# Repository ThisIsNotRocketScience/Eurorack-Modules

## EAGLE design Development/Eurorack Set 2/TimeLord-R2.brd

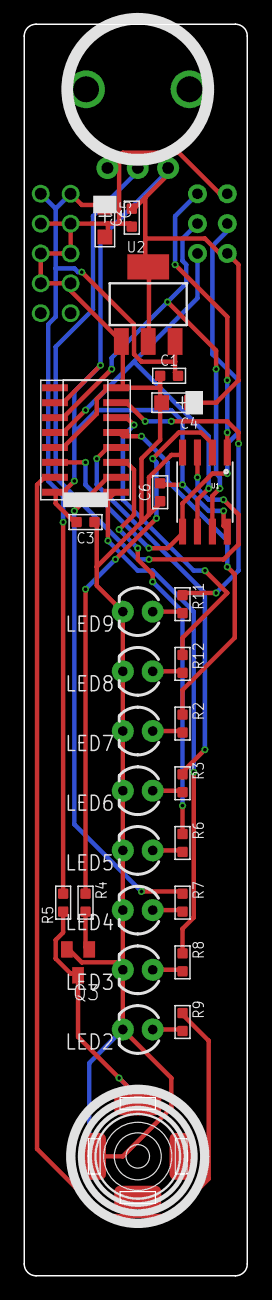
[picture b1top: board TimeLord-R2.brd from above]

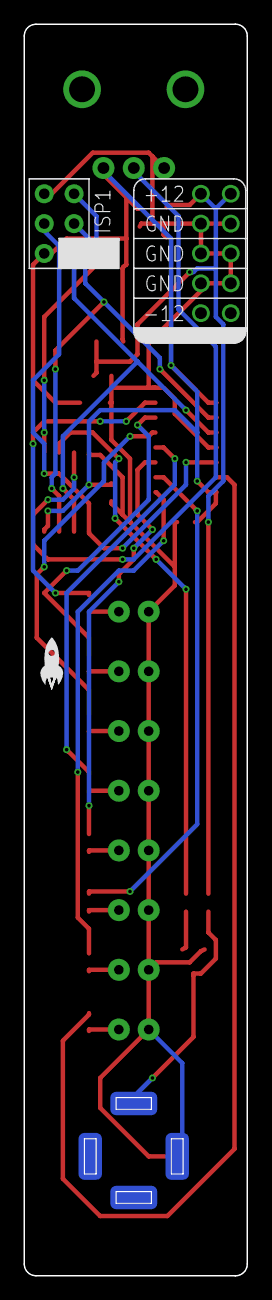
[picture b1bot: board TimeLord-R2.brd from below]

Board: 2 copper layers, 19.0 x 106.5 mm, 34 parts (3 on the bottom side), 27 nets.

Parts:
C1, C2, C3, C6: 100nF; C0603
C4, C5: 10uF; AVX-A
IC2: IC_74HC595-SOIC-16; SOIC-16
ISP1: AVRISP-6; AVRISP
LED2, LED3, LED4, LED5, LED6, LED7, LED8, LED9: WHITE; LED3MM
Q3: MMBT3904; SOT23-BEC
R2, R3, R6, R7, R8, R9, R11, R12: 50; R0603
R4: 100k; R0603
R5: 10k; R0603
U1: Tiny85-20-SMT; SO08-EIAJ
U2: CJ1117-5.0-1310170P1; SOT223
U$1: POWER_SIMPLE10-OTHERSIDE; POWER_10_LABELSOTHERSIDE
U$2: EURORACK_PCB4HP; EURORACK4HPPCB
U$3: CLOCK; 3.5MM-JACK-SWITCH-13MM-OUTPUT
U$4: SPEED; OG-POTS_ALPS_POT_VERTICAL
U$5: JUSTATINYROCKET

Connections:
5V: C2.2, C3.2, C4.+, C6.2, IC2.10, IC2.16, ISP1.2, U1.8, U2.2, U2.TER, U$4.P$3
12V: C1.2, C5.+, R5.2, U2.3, U$1.9, U$1.10
CLOCKJACK: Q3.C, R5.1, U$3.TIP@1, U$3.TIP@2
CLOCKOUT: R4.1, U1.2
CLOCKPOT: U1.3, U$4.P$2
GND: C1.1, C2.1, C3.1, C4.-, C5.-, C6.1, IC2.8, IC2.13, ISP1.6, LED2.K, LED3.K, LED4.K, LED5.K, LED6.K, LED7.K, LED8.K, LED9.K, Q3.E, U1.4, U2.1, U$1.3, U$1.4, U$1.5, U$1.6, U$1.7, U$1.8, U$3.RING@1, U$3.RING@2, U$4.P$1
LEDB1: IC2.15, R9.1
LEDB2: IC2.1, R8.1
LEDB3: IC2.2, R7.1
LEDB4: IC2.3, R6.1
LEDB5: IC2.4, R3.1
LEDB6: IC2.5, R2.1
LEDB7: IC2.6, R12.1
LEDB8: IC2.7, R11.1
LEDCLOCK: IC2.11, ISP1.3, U1.7
LEDDAT: IC2.14, ISP1.4, U1.5
LEDLATCH: IC2.12, ISP1.1, U1.6
unnamed: LED9.A, R11.2
unnamed: LED8.A, R12.2
unnamed: LED7.A, R2.2
unnamed: LED6.A, R3.2
unnamed: LED5.A, R6.2
unnamed: LED4.A, R7.2
unnamed: LED3.A, R8.2
unnamed: LED2.A, R9.2
unnamed: Q3.B, R4.2
RESET: ISP1.5, U1.1

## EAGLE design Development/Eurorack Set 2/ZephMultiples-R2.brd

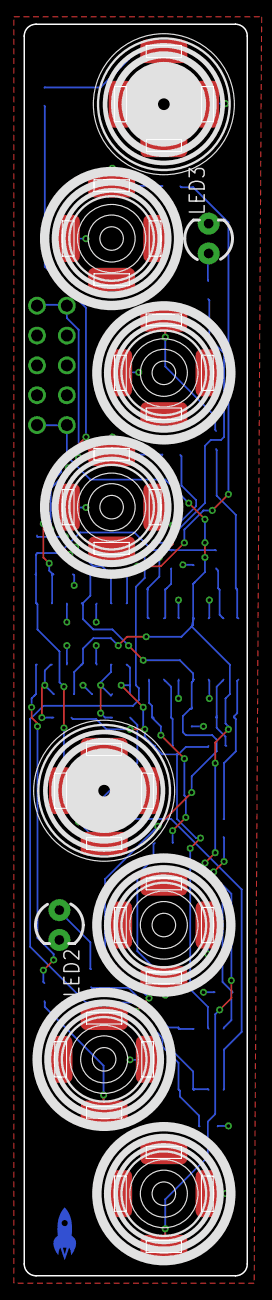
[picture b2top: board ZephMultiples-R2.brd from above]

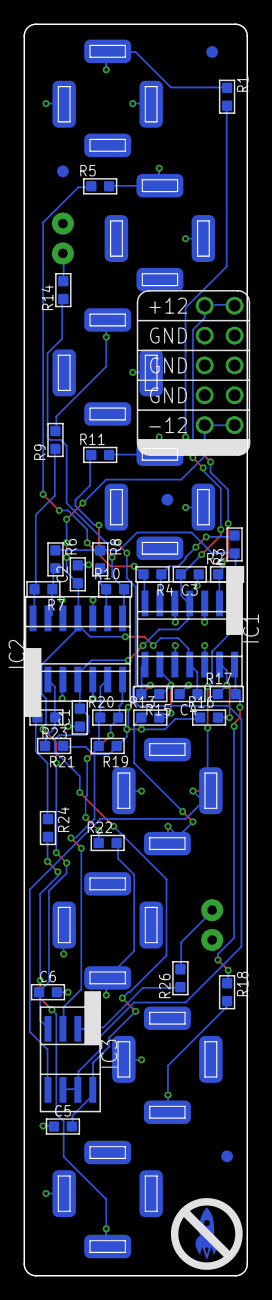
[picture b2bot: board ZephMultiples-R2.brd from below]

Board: 2 copper layers, 19.0 x 106.5 mm, 50 parts (39 on the bottom side), 31 nets.

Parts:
C1, C2, C3, C4, C5, C6: 100n; C0603
I1: In 1; 3.5MM-JACK-SWITCH-13MM-INPUT
I2: In 2; 3.5MM-JACK-SWITCH-13MM-INPUT
IC1, IC2: TL074D; SO14
IC3: TL072; SO08
LED2, LED3: REDBLUE; LED3MM
O1-1, O1-2, O1-3, O2-1, O2-2, O2-3: 3.5MM-JACK-SWITCH-13MM-OUTPUT
R1, R2, R3, R4, R6, R7, R8, R10, R13, R15, R16, R17, R19, R20, R21, R23: 100k; R0603
R5, R9, R11, R18, R22, R24: 51; R0603
R14, R26: 1k; R0603
U$1: SMALLROCKET
U$2, U$3, U$4, U$5: FIDUCIAL; FIDUCIAL_1MM
U$15: EURORACK_PCB4HP; EURORACK4HPPCB
U$16: POWER_SIMPLE10-OTHERSIDE; POWER_10_LABELSOTHERSIDE

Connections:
12V: C1.2, C3.2, C5.2, IC1.4, IC2.4, IC3.8, U$16.9, U$16.10
-12V: C2.1, C4.1, C6.1, IC1.11, IC2.11, IC3.4, U$16.1, U$16.2
GND: C1.1, C2.2, C3.1, C4.2, C5.1, C6.2, I1.RING@1, I1.RING@2, I1.SWITCH@1, I1.SWITCH@2, I2.RING@1, I2.RING@2, IC1.3, IC1.5, IC1.10, IC1.12, IC2.3, IC2.5, IC2.10, IC2.12, LED2.K, LED3.K, O1-1.RING@1, O1-1.RING@2, O1-2.RING@1, O1-2.RING@2, O1-3.RING@1, O1-3.RING@2, O2-1.RING@1, O2-1.RING@2, O2-2.RING@1, O2-2.RING@2, O2-3.RING@1, O2-3.RING@2, U$16.3, U$16.4, U$16.5, U$16.6, U$16.7, U$16.8
LED2DRIVE: IC3.6, IC3.7, R14.1
LED3DRIVE: IC3.1, IC3.2, R26.1
unnamed: I1.TIP@1, I1.TIP@2, R1.1
unnamed: IC1.2, R1.2, R2.1
unnamed: I2.SWITCH@1, I2.SWITCH@2, IC1.1, IC3.5, R2.2, R3.1, R6.1, R8.1
unnamed: IC1.6, R3.2, R4.1
unnamed: IC1.7, R4.2, R5.1
unnamed: IC2.13, R6.2, R7.1
unnamed: IC2.9, R8.2, R10.1
unnamed: IC2.14, R7.2, R9.1
unnamed: IC2.8, R10.2, R11.1
unnamed: LED3.A, R14.2
unnamed: O1-1.TIP@1, O1-1.TIP@2, R5.2
unnamed: O1-2.TIP@1, O1-2.TIP@2, R9.2
unnamed: O1-3.TIP@1, O1-3.TIP@2, R11.2
unnamed: I2.TIP@1, I2.TIP@2, R13.1
unnamed: IC1.9, R13.2, R15.1
unnamed: IC1.8, IC3.3, R15.2, R16.1, R19.1, R21.1
unnamed: IC1.13, R16.2, R17.1
unnamed: IC1.14, R17.2, R18.1
unnamed: IC2.6, R19.2, R20.1
unnamed: IC2.2, R21.2, R23.1
unnamed: IC2.7, R20.2, R22.1
unnamed: IC2.1, R23.2, R24.1
unnamed: LED2.A, R26.2
unnamed: O2-1.TIP@1, O2-1.TIP@2, R18.2
unnamed: O2-2.TIP@1, O2-2.TIP@2, R22.2
unnamed: O2-3.TIP@1, O2-3.TIP@2, R24.2

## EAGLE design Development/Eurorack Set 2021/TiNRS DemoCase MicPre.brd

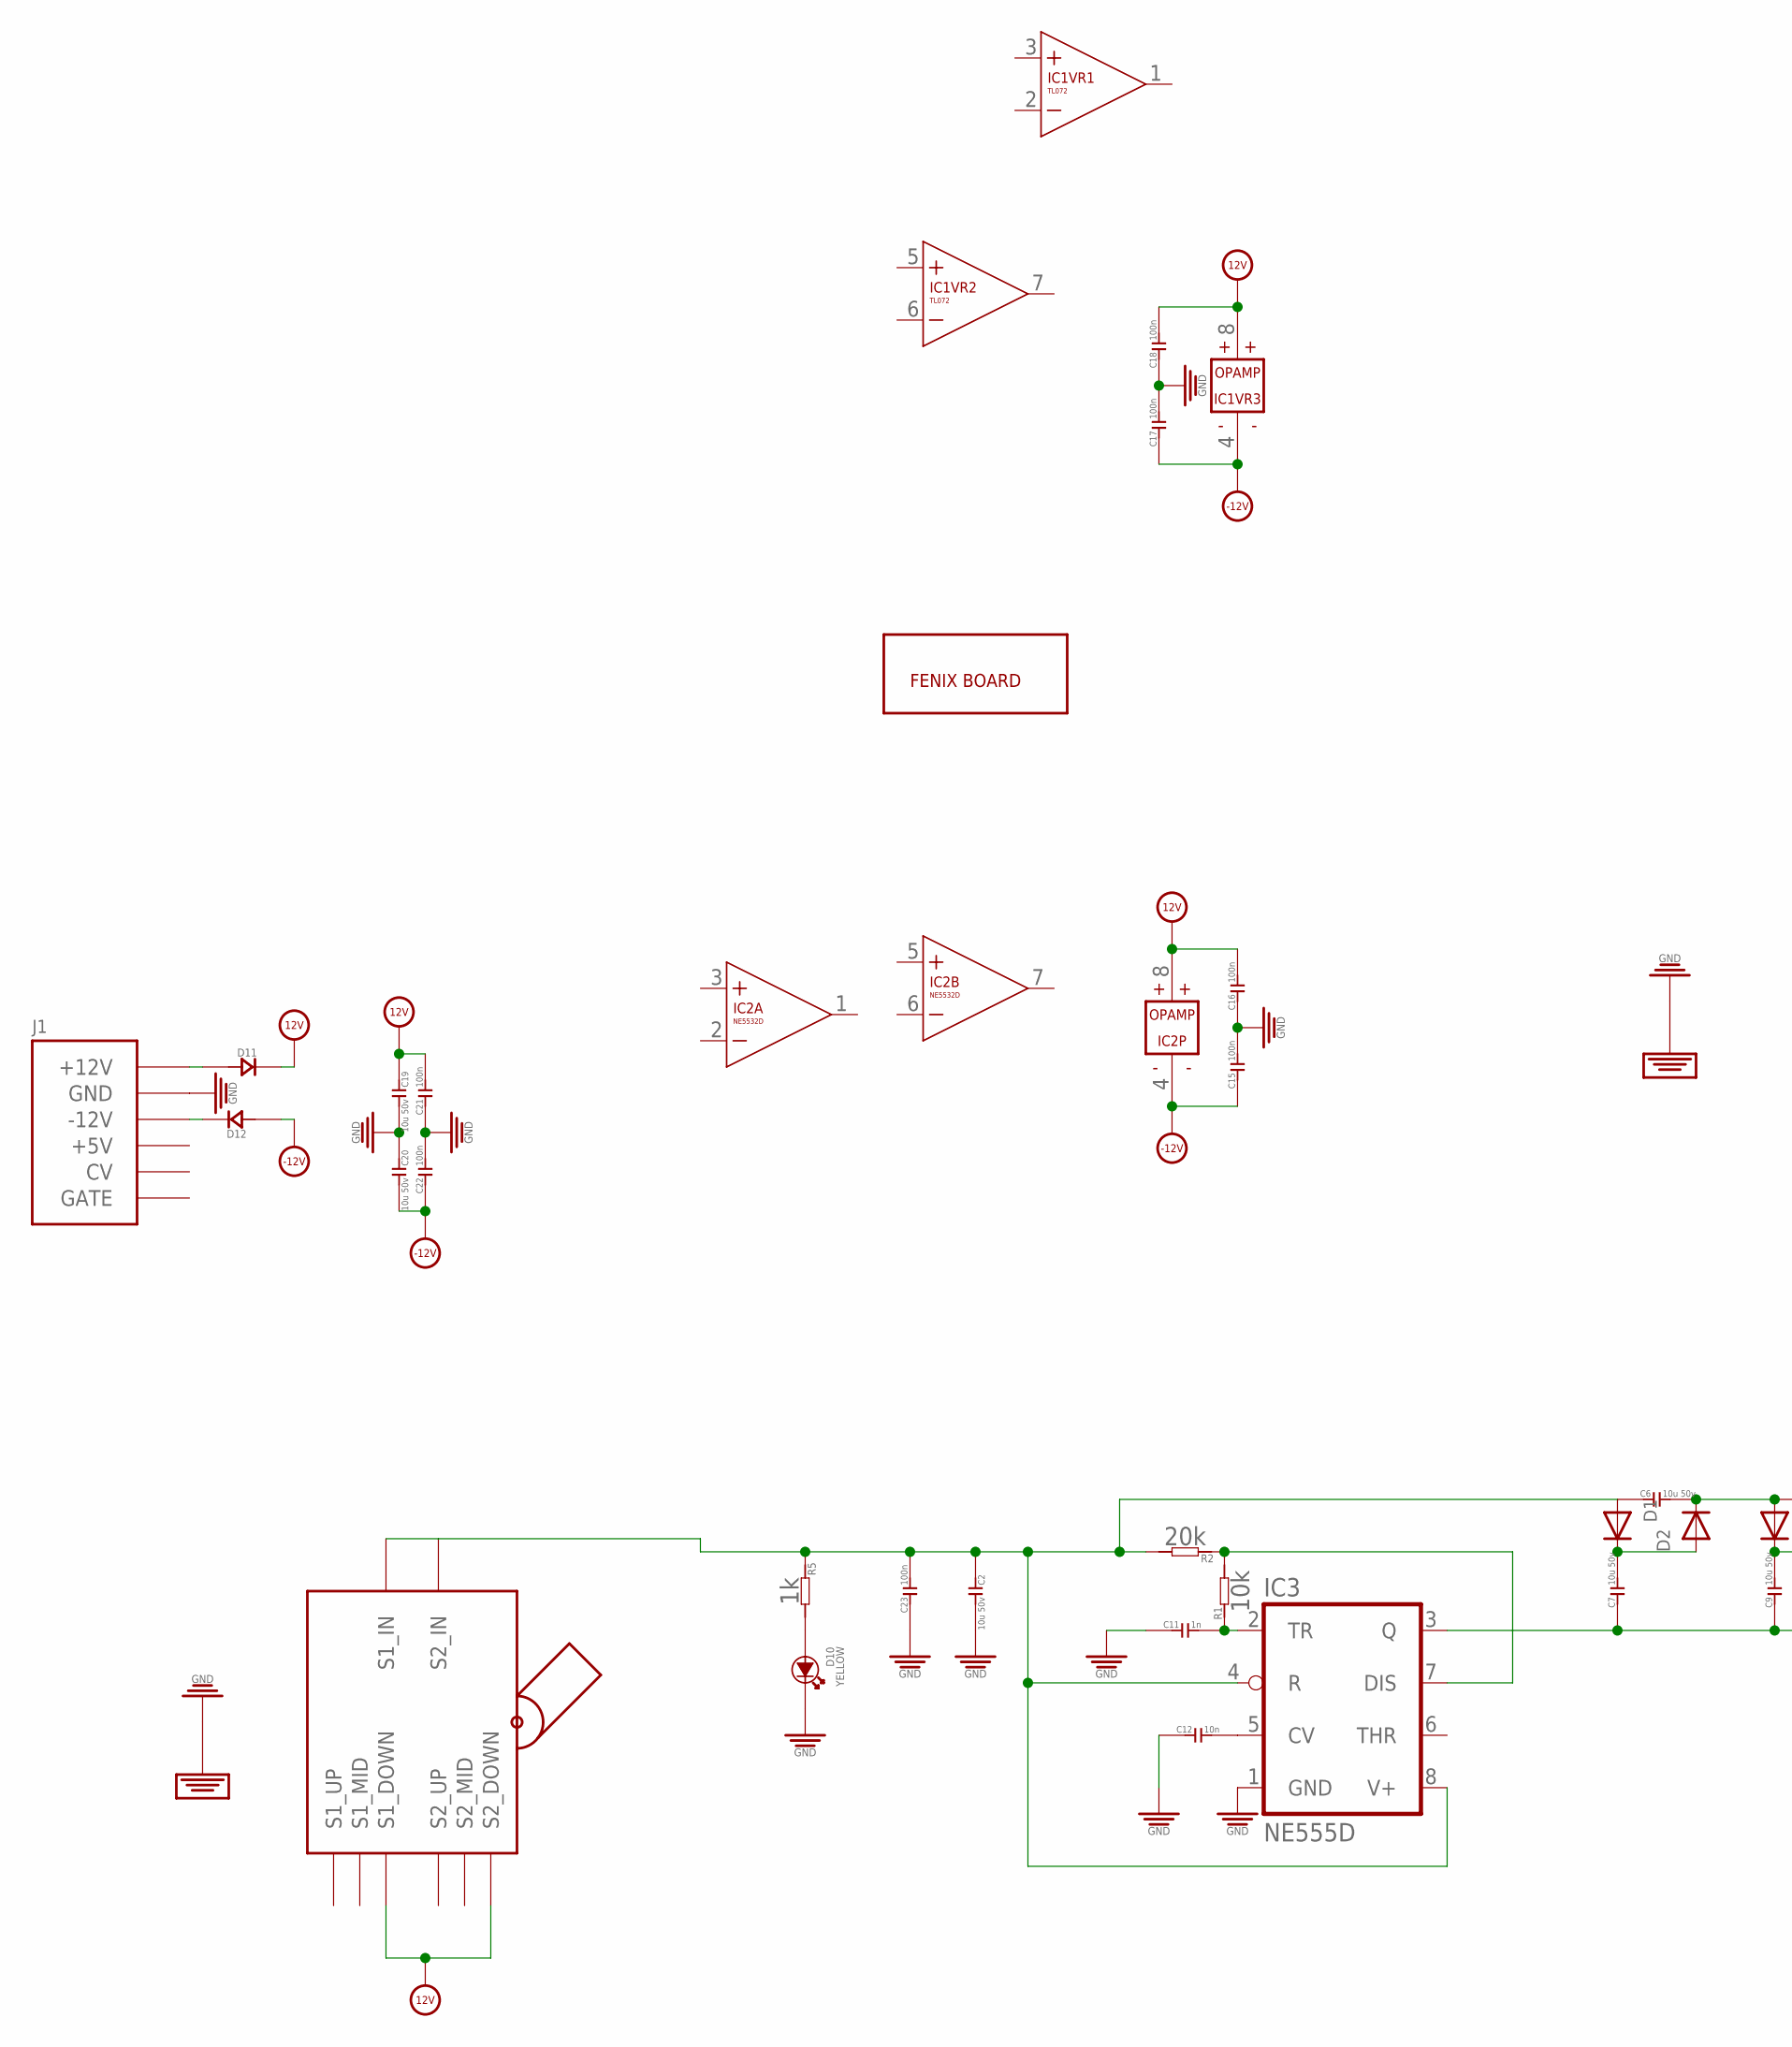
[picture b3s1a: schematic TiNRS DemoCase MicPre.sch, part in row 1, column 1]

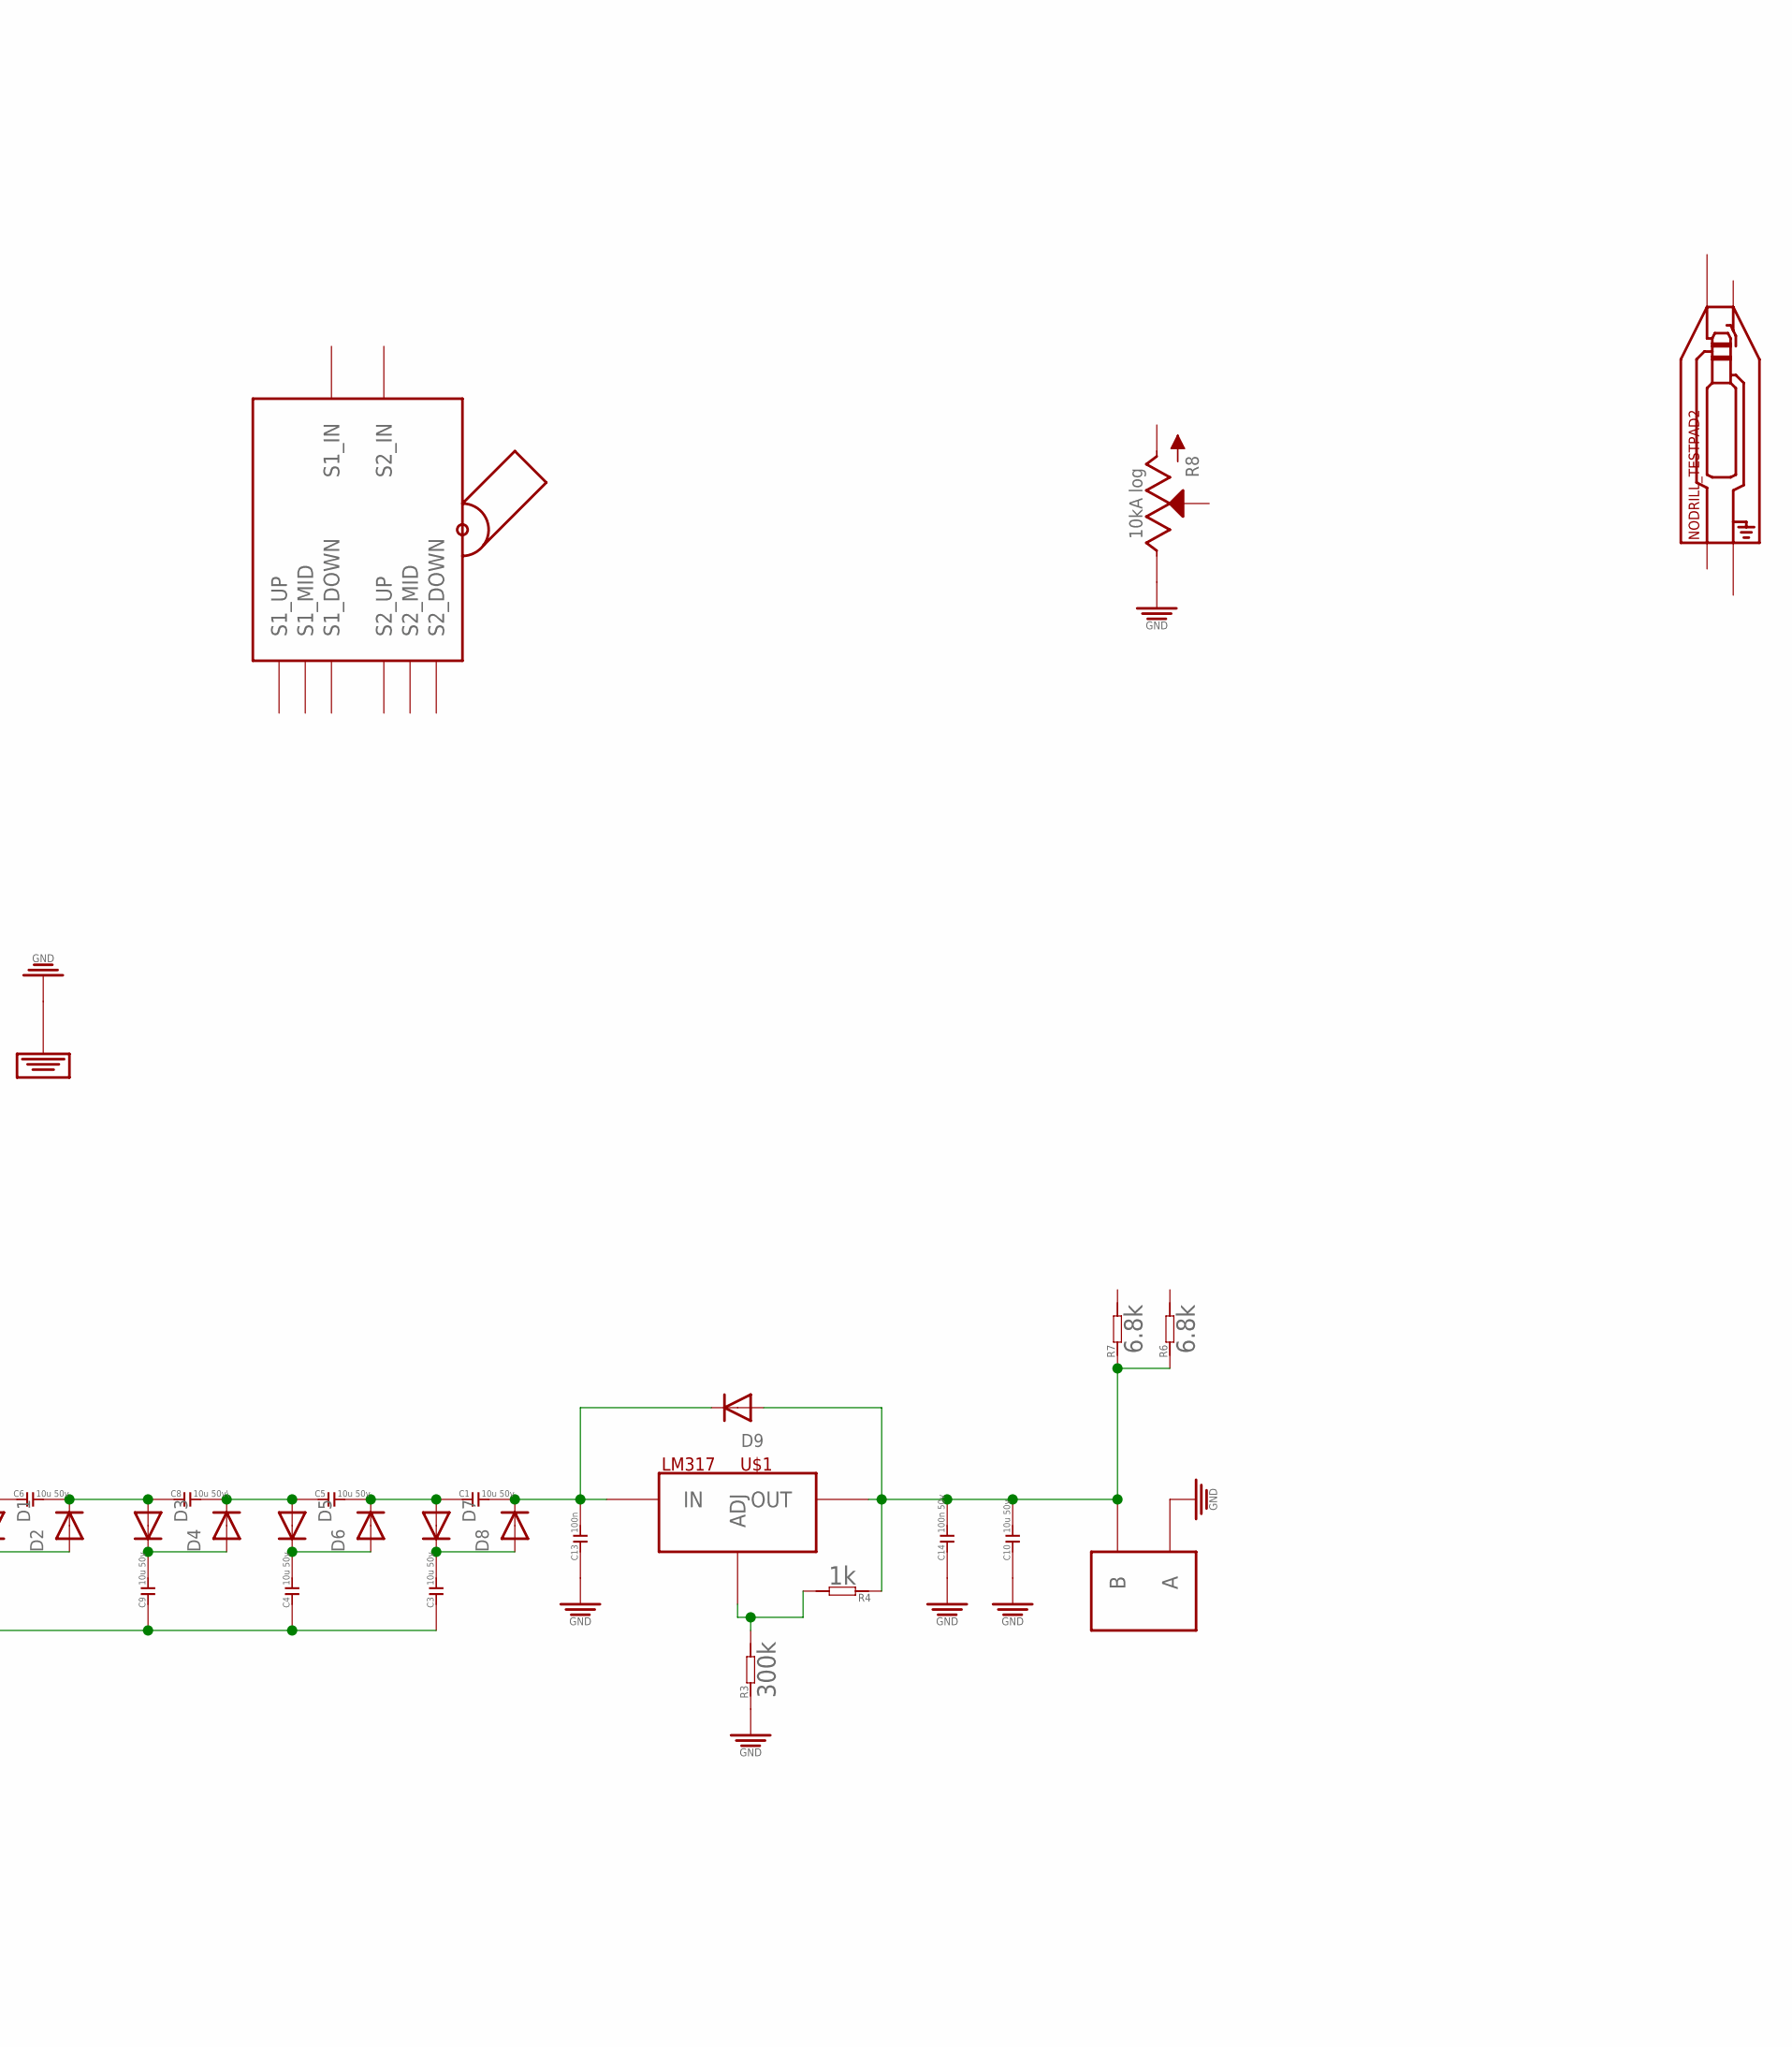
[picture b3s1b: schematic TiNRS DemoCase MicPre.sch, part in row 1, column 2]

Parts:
C1, C2, C3, C4, C5, C6, C7, C9, C10, C19, C20: 10u 50v; C3216
C8: 10u 50v\; C3216
C11: 1n; C0603
C12: 10n; C0603
C13, C15, C16, C17, C18, C21, C22, C23: 100n; C0603
C14: 100n 50v; C0603
D1, D2, D3, D4, D5, D6, D7, D8, D9: DIODESOD-123; SOD-123
D10: YELLOW; 3MMLED
D11, D12: D-SMA; DO-214AC
IC1: TL072; SO08
IC2: NE5532D; SO08
IC3: NE555D; SO08
J1: POWER_SHROUDED_NOTEXT; POWER_16_SHROUDED_NOTEXT
NODRILL_TESTPAD2: AUDIO-JACK_SMALLSYMBOL; 3.5MM-JACK-SWITCH-13MM-NOHOLES-TESTPAD
R1: 10k; R0603
R2: 20k; R0603
R3: 300k; R0603
R4, R5: 1k; R0603
R6, R7: 6.8k; R0603
R8: 10kA log; ALPS_POT_SQUAREHOLES
U$1: LM317; SOT-223
U$2: TESTPOINT_DUAL_PTH; TESTPAD_DUAL_PTH
U$3, U$4: TS-23E01
U$14: FENIXBOARDS2U; FENIX_2U_84HP

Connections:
12V: C16.2, C18.2, C19.P$1 (1), C21.2, D11.2 (-), IC1.8 (V+), IC2.8 (V+), U$3.S1_DOWN, U$3.S2_DOWN
-12V: C15.1, C17.1, C20.P$2 (2), C22.1, D12.1 (+), IC1.4 (V-), IC2.4 (V-)
GND: C2.P$2 (2), C10.P$1 (1), C11.1, C12.1, C13.1, C14.1, C15.2, C16.1, C17.2, C18.1, C19.P$2 (2), C20.P$1 (1), C21.1, C22.2, C23.1, D10.-, IC3.1 (GND), J1.3 (GND), J1.4 (GND), J1.5 (GND), J1.6 (GND), J1.7 (GND), J1.8 (GND), R3.1, R8.P$1 (E), U$2.P$1 (A), U$3.P$9 (GND), U$3.P$10 (GND), U$3.P$11 (GND), U$3.P$12 (GND), U$4.P$9 (GND), U$4.P$10 (GND), U$4.P$11 (GND), U$4.P$12 (GND)
unnamed: C3.P$1 (1), C4.P$1 (1), C7.P$1 (1), C9.P$1 (1), IC3.3 (Q)
unnamed: C7.P$2 (2), D1.C, D2.A
unnamed: D10.+, R5.2
unnamed: C6.P$2 (2), C8.P$1 (1), D2.C, D3.A
unnamed: C9.P$2 (2), D3.C, D4.A
unnamed: C5.P$1 (1), C8.P$2 (2), D4.C, D5.A
unnamed: C4.P$2 (2), D5.C, D6.A
unnamed: C1.P$1 (1), C5.P$2 (2), D6.C, D7.A
unnamed: C3.P$2 (2), D7.C, D8.A
unnamed: D11.1 (+), J1.9 (+12V), J1.10 (+12V)
unnamed: C1.P$2 (2), C13.2, D8.C, D9.C, U$1.3 (IN)
unnamed: D12.2 (-), J1.1 (-12V), J1.2 (-12V)
unnamed: C12.2, IC3.5 (CV)
unnamed: C11.2, IC3.2 (TR), R1.1
unnamed: IC3.7 (DIS), R1.2, R2.1
unnamed: R3.2, R4.2, U$1.1 (ADJ)
PHANTOM48V: C10.P$2 (2), C14.2, D9.A, R4.1, R6.1, R7.1, U$1.2 (OUT), U$1.PAD (OUT), U$2.P$2 (B)
PHANTOMSRC: C2.P$1 (1), C6.P$1 (1), C23.2, D1.A, IC3.4 (R), IC3.8 (V+), R2.2, R5.1, U$3.S1_SRC (S1_IN), U$3.S2_SRC (S2_IN)

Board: 2 copper layers, 53 parts (1 on the bottom side), 21 nets, no tracks yet.

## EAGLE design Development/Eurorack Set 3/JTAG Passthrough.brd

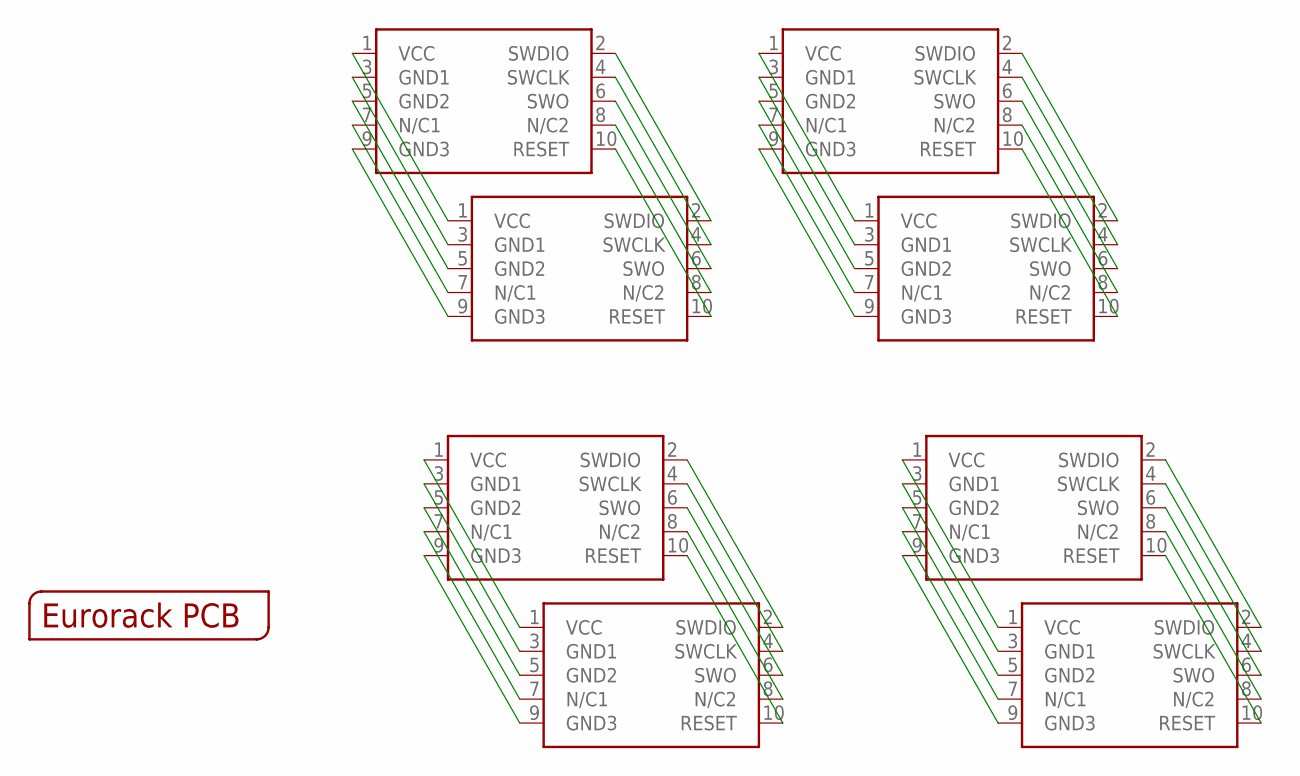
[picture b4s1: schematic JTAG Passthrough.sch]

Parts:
SWD1, SWD3, SWD5, SWD7: CORTEX_SWD; M50-3600542
SWD2, SWD4, SWD6, SWD8: CORTEX_SWDVERT_HOLE; SWD_VERTICAL_WITHHOLE
U$2: EURORACK_PCB2HP; EURORACK2HPPCB

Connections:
unnamed: SWD1.1 (VCC), SWD2.1 (VCC)
unnamed: SWD1.2 (SWDIO), SWD2.2 (SWDIO)
unnamed: SWD1.3 (GND1), SWD2.3 (GND1)
unnamed: SWD1.4 (SWCLK), SWD2.4 (SWCLK)
unnamed: SWD1.5 (GND2), SWD2.5 (GND2)
unnamed: SWD1.6 (SWO), SWD2.6 (SWO)
unnamed: SWD1.7 (N/C1), SWD2.7 (N/C1)
unnamed: SWD1.8 (N/C2), SWD2.8 (N/C2)
unnamed: SWD1.9 (GND3), SWD2.9 (GND3)
unnamed: SWD1.10 (RESET), SWD2.10 (RESET)
unnamed: SWD3.1 (VCC), SWD4.1 (VCC)
unnamed: SWD3.2 (SWDIO), SWD4.2 (SWDIO)
unnamed: SWD3.3 (GND1), SWD4.3 (GND1)
unnamed: SWD3.4 (SWCLK), SWD4.4 (SWCLK)
unnamed: SWD3.5 (GND2), SWD4.5 (GND2)
unnamed: SWD3.6 (SWO), SWD4.6 (SWO)
unnamed: SWD3.7 (N/C1), SWD4.7 (N/C1)
unnamed: SWD3.8 (N/C2), SWD4.8 (N/C2)
unnamed: SWD3.9 (GND3), SWD4.9 (GND3)
unnamed: SWD3.10 (RESET), SWD4.10 (RESET)
unnamed: SWD5.1 (VCC), SWD6.1 (VCC)
unnamed: SWD5.2 (SWDIO), SWD6.2 (SWDIO)
unnamed: SWD5.3 (GND1), SWD6.3 (GND1)
unnamed: SWD5.4 (SWCLK), SWD6.4 (SWCLK)
unnamed: SWD5.5 (GND2), SWD6.5 (GND2)
unnamed: SWD5.6 (SWO), SWD6.6 (SWO)
unnamed: SWD5.7 (N/C1), SWD6.7 (N/C1)
unnamed: SWD5.8 (N/C2), SWD6.8 (N/C2)
unnamed: SWD5.9 (GND3), SWD6.9 (GND3)
unnamed: SWD5.10 (RESET), SWD6.10 (RESET)
unnamed: SWD7.1 (VCC), SWD8.1 (VCC)
unnamed: SWD7.2 (SWDIO), SWD8.2 (SWDIO)
unnamed: SWD7.3 (GND1), SWD8.3 (GND1)
unnamed: SWD7.4 (SWCLK), SWD8.4 (SWCLK)
unnamed: SWD7.5 (GND2), SWD8.5 (GND2)
unnamed: SWD7.6 (SWO), SWD8.6 (SWO)
unnamed: SWD7.7 (N/C1), SWD8.7 (N/C1)
unnamed: SWD7.8 (N/C2), SWD8.8 (N/C2)
unnamed: SWD7.9 (GND3), SWD8.9 (GND3)
unnamed: SWD7.10 (RESET), SWD8.10 (RESET)

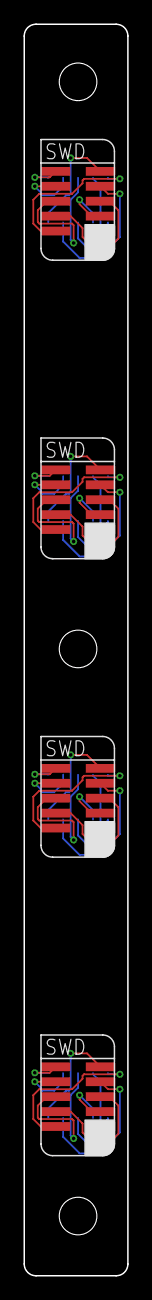
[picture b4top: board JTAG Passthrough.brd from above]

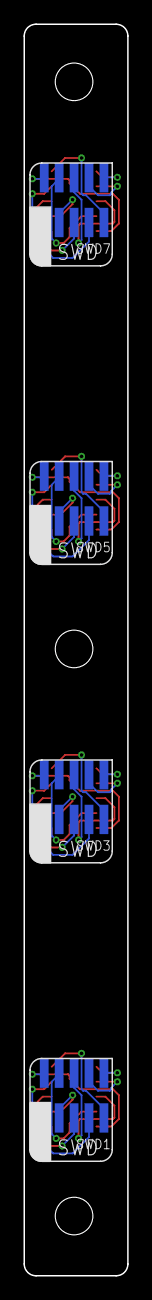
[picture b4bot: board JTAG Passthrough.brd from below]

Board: 2 copper layers, 8.8 x 106.5 mm, 9 parts (4 on the bottom side), 40 nets.

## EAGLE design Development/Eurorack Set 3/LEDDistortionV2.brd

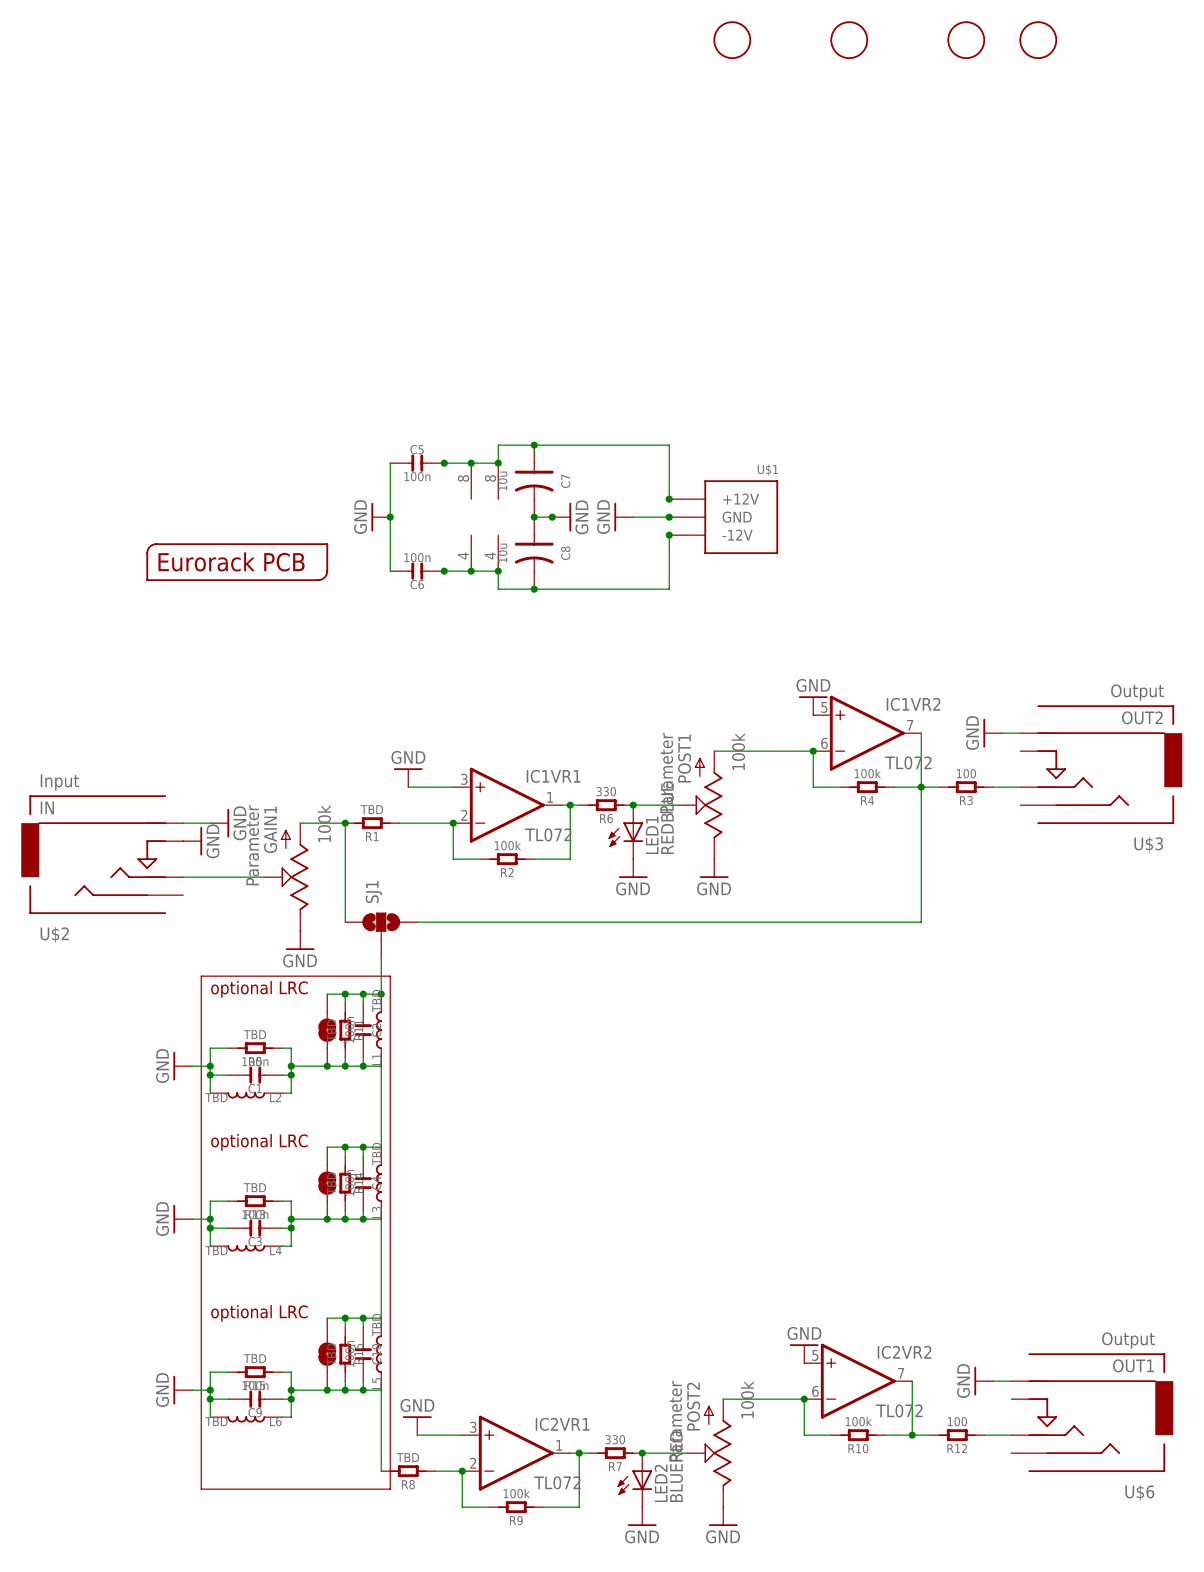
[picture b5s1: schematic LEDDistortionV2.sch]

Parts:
C1, C2, C3, C4, C5, C6, C9, C10: 100n; C0805
C7, C8: 10u; AVX-A
GAIN1: 100k; OG-POTS_ALPS_POT_VERTICAL
IC1, IC2: TL072; SO08
L1, L2, L3, L4, L5, L6: TBD; L0420
LED1: REDBLUE; LED3MM
LED2: BLUERED; LED3MM
POST1, POST2: 100k; OG-POTS_ALPS_POT_VERTICAL
R1, R5, R8, R11, R13, R14, R15, R16: TBD; C0805
R2, R4, R9, R10: 100k; C0805
R3, R12: 100; C0805
R6, R7: 330; C0805
SJ1: SOLDERJUMPER_2WAYPASTE1&2; SJ_3_PASTE1&2
SJ2, SJ3, SJ4: SOLDERJUMPERNC; SJ_2S
U$1: POWER_SIMPLE10; POWER_10
U$2: IN; 3.5MM-JACK-SWITCH-13MM-INPUT
U$3: OUT2; 3.5MM-JACK-SWITCH-13MM-OUTPUT
U$4: EURORACK_PCB4HP; EURORACK4HPPCB
U$5, U$7, U$8, U$9: FIDUCIAL; FIDUCIAL_1MM
U$6: OUT1; 3.5MM-JACK-SWITCH-13MM-OUTPUT

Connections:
GND: C1.2, C3.2, C5.1, C6.2, C7.- (2), C8.+ (1), C9.2, GAIN1.P$1 (E), IC1.3 (+IN), IC1.5 (+IN), IC2.3 (+IN), IC2.5 (+IN), L2.2, L4.2, L6.2, LED1.K (C), LED2.K (C), POST1.P$1 (E), POST2.P$1 (E), R5.2, R13.2, R15.2, U$1.3 (GND), U$1.4 (GND), U$1.5 (GND), U$1.6 (GND), U$1.7 (GND), U$1.8 (GND), U$2.RING@3 (RING), U$2.SWITCH@3 (SWITCH), U$3.RING@3 (RING), U$6.RING@3 (RING)
unnamed: C2.1, L1.2, R11.1, SJ1.2, SJ2.2
unnamed: LED1.A, POST1.P$2 (S), R6.1
unnamed: GAIN1.P$3 (A), R1.2, SJ1.1
unnamed: IC1.6 (-IN), POST1.P$3 (A), R4.2
unnamed: R3.1, U$3.TIP@3 (TIP)
unnamed: GAIN1.P$2 (S), U$2.TIP@3 (TIP)
unnamed: LED2.A, POST2.P$2 (S), R7.1
unnamed: IC2.6 (-IN), POST2.P$3 (A), R10.2
unnamed: C1.1, C2.2, C4.1, L1.1, L2.1, L3.2, R5.1, R11.2, R14.1, SJ2.1, SJ3.2
unnamed: R12.1, U$6.TIP@3 (TIP)
unnamed: C9.1, C10.2, L5.1, L6.1, R8.2, R15.1, R16.2, SJ4.1
unnamed: C3.1, C4.2, C10.1, L3.1, L4.1, L5.2, R13.1, R14.2, R16.1, SJ3.1, SJ4.2
OP1NEG: IC1.2 (-IN), R1.1, R2.2
OP1NEG1: IC2.2 (-IN), R8.1, R9.2
OP1OUT: IC1.1 (OUT), R2.1, R6.2
OP1OUT1: IC2.1 (OUT), R7.2, R9.1
OP2OUT: IC1.7 (OUT), R3.2, R4.1, SJ1.3
OP2OUT1: IC2.7 (OUT), R10.1, R12.2
VNEG: C6.1, C8.- (2), IC1.4 (V-), IC2.4 (V-), U$1.1 (-12V), U$1.2 (-12V)
VPOS: C5.2, C7.+ (1), IC1.8 (V+), IC2.8 (V+), U$1.9 (+12V), U$1.10 (+12V)

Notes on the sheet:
optional LRC

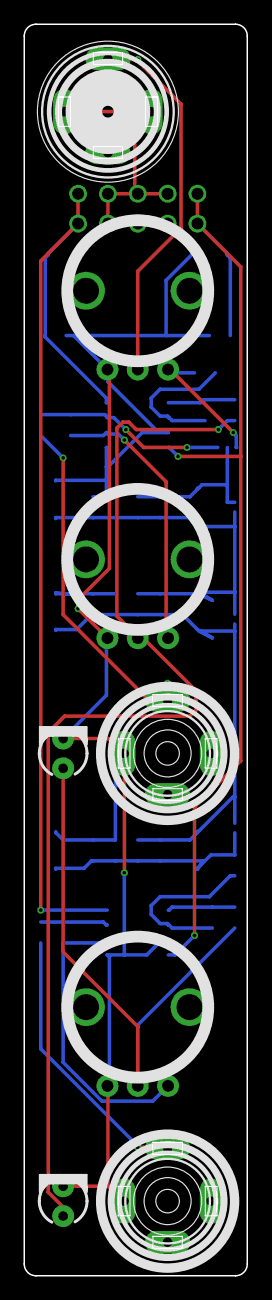
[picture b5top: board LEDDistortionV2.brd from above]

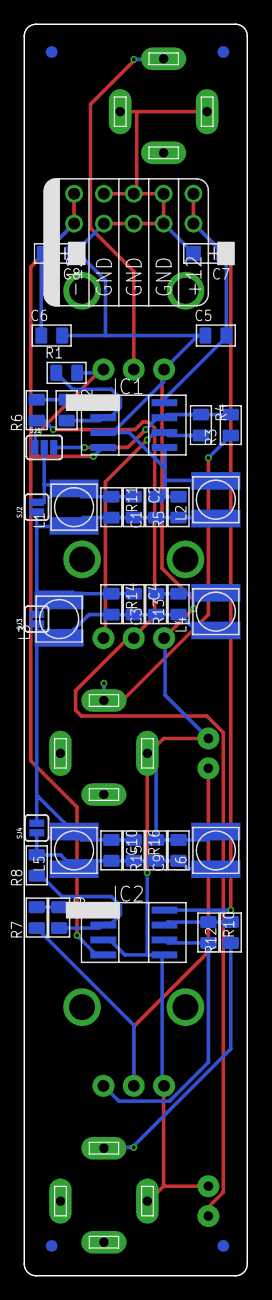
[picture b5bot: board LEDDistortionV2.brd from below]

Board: 2 copper layers, 19.0 x 106.5 mm, 52 parts (43 on the bottom side), 21 nets.

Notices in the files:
parts and their libraries:
SparkFun-LED: Licensing: CC v3.0 Share-Alike You are welcome to use this library for commercial purposes.
